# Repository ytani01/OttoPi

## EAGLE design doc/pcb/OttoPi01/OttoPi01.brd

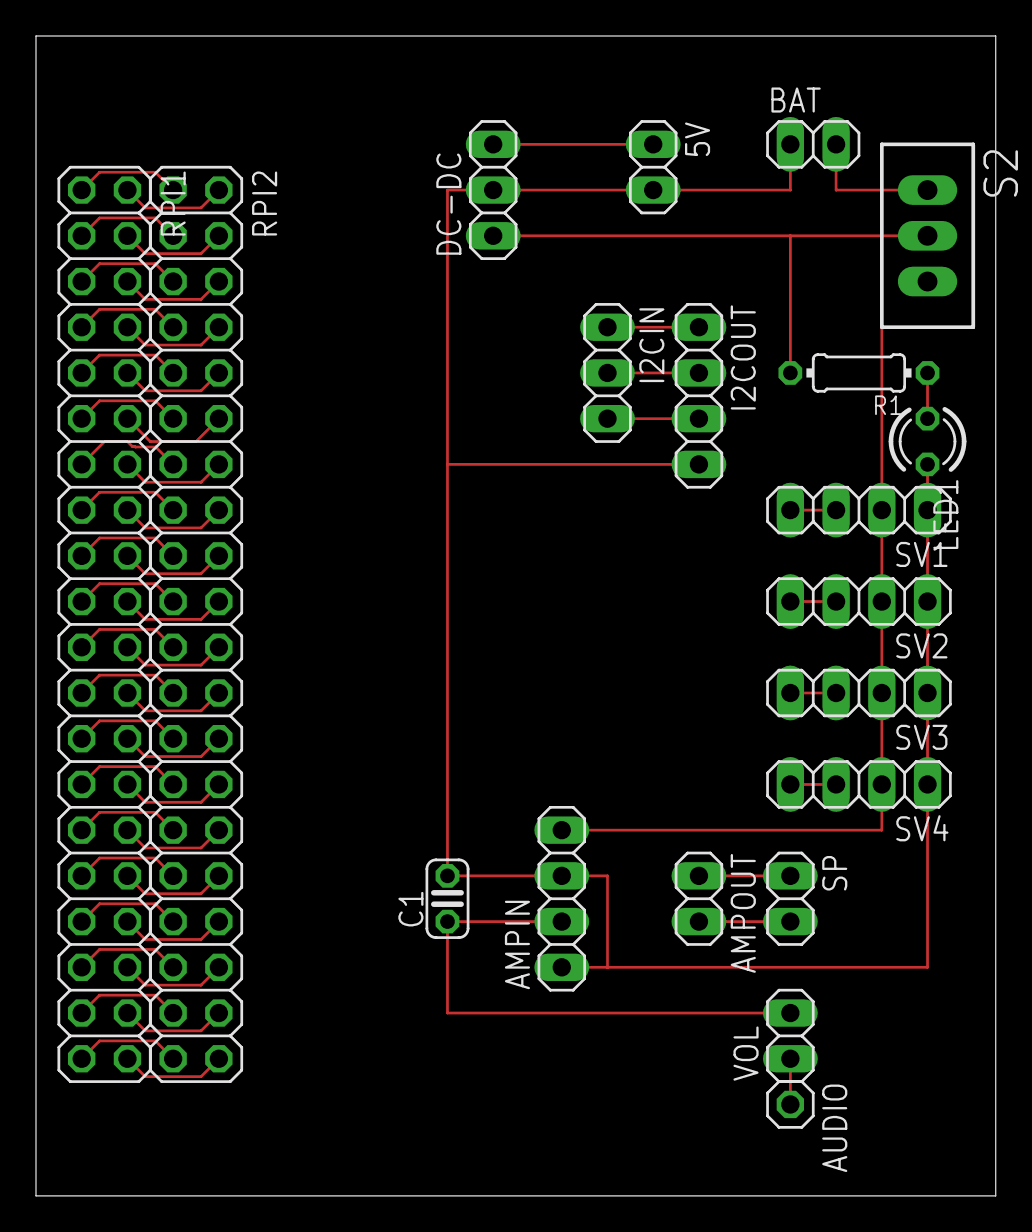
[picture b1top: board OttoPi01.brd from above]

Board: 2 copper layers, 53.3 x 64.4 mm, 20 parts (0 on the bottom side), 56 nets.

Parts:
5V: 1X02
AMPIN: 1X04
AMPOUT: 1X02
AUDIO: 1X01
BAT: 1X02
C1: C025-024X044
DC-DC: 1X03
I2CIN: 1X03
I2COUT: 1X04
LED1: LED3MM
R1: 0204/7
RPI1, RPI2: 2X20
S2: TL36PO; TL3XPO
SP: 1X02
SV1, SV2, SV3, SV4: 1X04
VOL: 1X02

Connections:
GND: 5V.2, AMPIN.1, AMPIN.3, BAT.1, C1.2, DC-DC.2, I2COUT.4, LED1.K, SV1.1, SV2.1, SV3.1, SV4.1
unnamed: I2CIN.1, I2COUT.1
unnamed: I2CIN.2, I2COUT.2
unnamed: I2CIN.3, I2COUT.3
unnamed: AMPOUT.2, SP.2
unnamed: 5V.1, DC-DC.3
unnamed: SV1.3, SV1.4
unnamed: BAT.2, S2.1
unnamed: AMPIN.2, C1.1, VOL.2
unnamed: SV2.3, SV2.4
unnamed: SV3.3, SV3.4
unnamed: SV4.3, SV4.4
unnamed: AMPOUT.1, SP.1
unnamed: AMPIN.4, DC-DC.1, R1.2, S2.2, SV1.2, SV2.2, SV3.2, SV4.2
unnamed: AUDIO.1, VOL.1
unnamed: LED1.A, R1.1
unnamed: RPI1.1, RPI2.1
unnamed: RPI1.3, RPI2.3
unnamed: RPI1.5, RPI2.5
unnamed: RPI1.7, RPI2.7
unnamed: RPI1.9, RPI2.9
unnamed: RPI1.11, RPI2.11
unnamed: RPI1.13, RPI2.13
unnamed: RPI1.15, RPI2.15
unnamed: RPI1.17, RPI2.17
unnamed: RPI1.19, RPI2.19
unnamed: RPI1.21, RPI2.21
unnamed: RPI1.23, RPI2.23
unnamed: RPI1.25, RPI2.25
unnamed: RPI1.27, RPI2.27
unnamed: RPI1.29, RPI2.29
unnamed: RPI1.31, RPI2.31
unnamed: RPI1.33, RPI2.33
unnamed: RPI1.35, RPI2.35
unnamed: RPI1.37, RPI2.37
unnamed: RPI1.39, RPI2.39
unnamed: RPI1.2, RPI2.2
unnamed: RPI1.4, RPI2.4
unnamed: RPI1.6, RPI2.6
unnamed: RPI1.8, RPI2.8
unnamed: RPI1.10, RPI2.10
unnamed: RPI1.12, RPI2.12
unnamed: RPI1.14, RPI2.14
unnamed: RPI1.16, RPI2.16
unnamed: RPI1.18, RPI2.18
unnamed: RPI1.20, RPI2.20
unnamed: RPI1.22, RPI2.22
unnamed: RPI1.24, RPI2.24
unnamed: RPI1.26, RPI2.26
unnamed: RPI1.28, RPI2.28
unnamed: RPI1.30, RPI2.30
unnamed: RPI1.32, RPI2.32
unnamed: RPI1.34, RPI2.34
unnamed: RPI1.36, RPI2.36
unnamed: RPI1.38, RPI2.38
unnamed: RPI1.40, RPI2.40

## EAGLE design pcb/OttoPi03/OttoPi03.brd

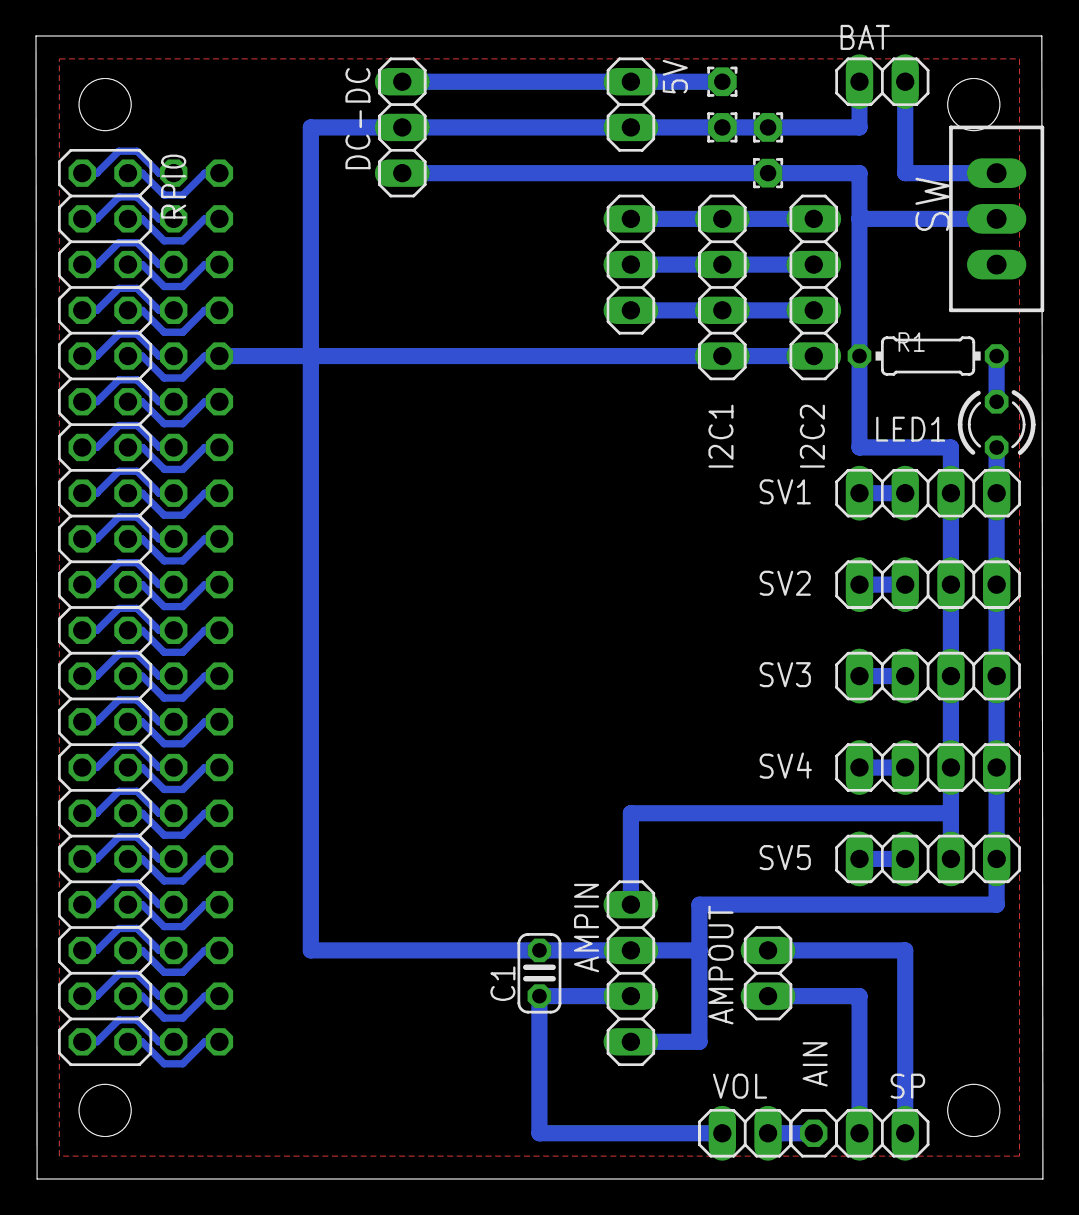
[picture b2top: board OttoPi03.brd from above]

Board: 2 copper layers, 55.9 x 63.5 mm, 26 parts (1 on the bottom side), 56 nets.

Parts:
5V: 1X02
5V_A: 1,6/0,9
AIN: 1X01
AMPIN: 1X04
AMPOUT: 1X02
BAT: 1X02
BAT_B: 1,6/0,9
C1: C025-024X044
DC-DC: 1X03
EXT: 2X20
GND_A: 1,6/0,9
GND_B: 1,6/0,9
I2C1, I2C2: 1X04
I2CIN: 1X03
LED1: LED3MM
R1: 0204/7
RPI0: 2X20
SP: 1X02
SV1, SV2, SV3, SV4, SV5: 1X04
SW: TL36PO; TL3XPO
VOL: 1X02

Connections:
3V3: I2C1.1, I2C2.1, I2CIN.1
4V: AMPIN.4, BAT_B.1, DC-DC.1, R1.2, SV1.2, SV2.2, SV3.2, SV4.2, SV5.2, SW.2
5V: 5V.1, 5V_A.1, DC-DC.3
AIN1: AIN.1, VOL.1
AIN2: AMPIN.2, C1.1, VOL.2
BAT+: BAT.2, SW.1
GND: 5V.2, AMPIN.1, AMPIN.3, BAT.1, C1.2, DC-DC.2, EXT.9, GND_A.1, GND_B.1, I2C1.4, I2C2.4, LED1.K, RPI0.10, SV1.1, SV2.1, SV3.1, SV4.1, SV5.1
unnamed: EXT.2, RPI0.1
unnamed: I2C1.2, I2C2.2, I2CIN.2
unnamed: I2C1.3, I2C2.3, I2CIN.3
unnamed: EXT.4, RPI0.3
unnamed: EXT.6, RPI0.5
unnamed: EXT.1, RPI0.2
unnamed: EXT.3, RPI0.4
unnamed: EXT.5, RPI0.6
unnamed: EXT.7, RPI0.8
unnamed: EXT.8, RPI0.7
unnamed: EXT.10, RPI0.9
unnamed: EXT.12, RPI0.11
unnamed: EXT.14, RPI0.13
unnamed: EXT.16, RPI0.15
unnamed: LED1.A, R1.1
unnamed: EXT.18, RPI0.17
unnamed: EXT.20, RPI0.19
unnamed: EXT.22, RPI0.21
unnamed: EXT.24, RPI0.23
unnamed: EXT.26, RPI0.25
unnamed: EXT.28, RPI0.27
unnamed: EXT.30, RPI0.29
unnamed: EXT.32, RPI0.31
unnamed: EXT.34, RPI0.33
unnamed: EXT.36, RPI0.35
unnamed: EXT.38, RPI0.37
unnamed: EXT.40, RPI0.39
unnamed: EXT.11, RPI0.12
unnamed: EXT.13, RPI0.14
unnamed: EXT.15, RPI0.16
unnamed: EXT.39, RPI0.40
unnamed: EXT.37, RPI0.38
unnamed: EXT.35, RPI0.36
unnamed: EXT.33, RPI0.34
unnamed: EXT.31, RPI0.32
unnamed: EXT.29, RPI0.30
unnamed: EXT.27, RPI0.28
unnamed: EXT.25, RPI0.26
unnamed: EXT.23, RPI0.24
unnamed: EXT.21, RPI0.22
unnamed: EXT.17, RPI0.18
unnamed: EXT.19, RPI0.20
SP+: AMPOUT.1, SP.1
SP-: AMPOUT.2, SP.2
SV1: SV1.3, SV1.4
SV2: SV2.3, SV2.4
SV3: SV3.3, SV3.4
SV4: SV4.3, SV4.4
SV5: SV5.3, SV5.4

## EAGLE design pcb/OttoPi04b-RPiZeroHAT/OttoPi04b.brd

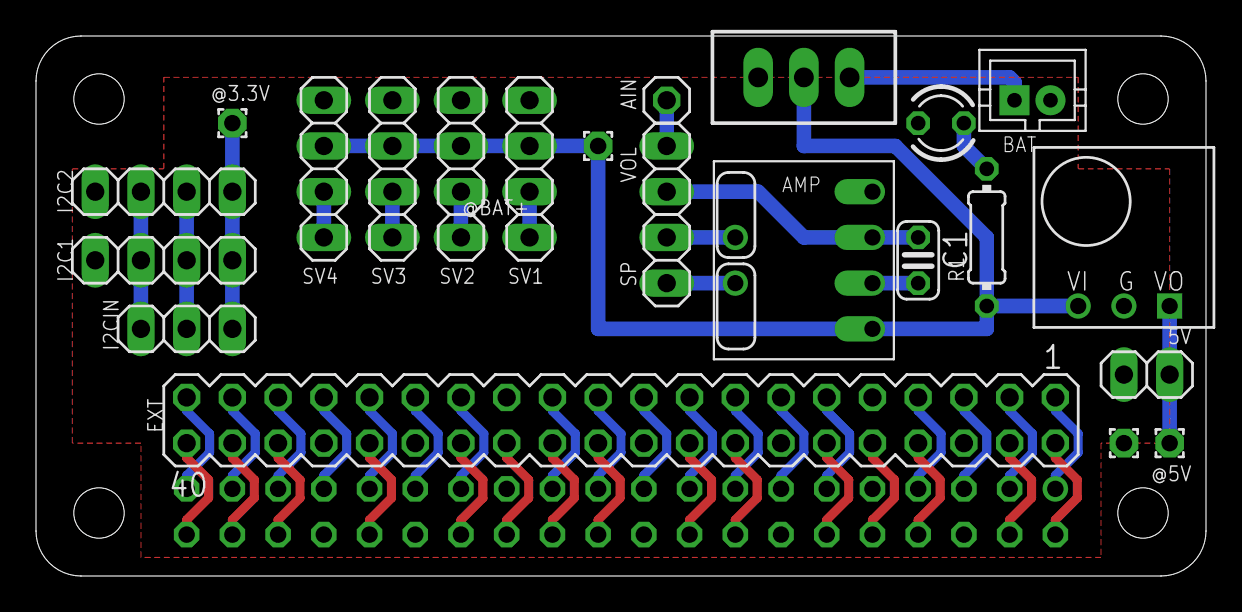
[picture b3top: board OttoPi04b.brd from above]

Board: 2 copper layers, 65.0 x 30.0 mm, 24 parts (1 on the bottom side), 48 nets.

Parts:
5V: 1X02
@3.3V, @5V: 1,6/0,9
@BAT+: 1,6/0,9
AIN: 1X01
AMP: PAM8012MOD; PAM8012MOD-A
BAT: JST-PH2
C1: C025-024X044
DCDC1: DCDC-5V-0.48A
EXT: MA20-2
I2C1, I2C2: 1X04
I2CIN: 1X03
LED1: LED3MM
PAD2: 1,6/0,9
R1: 1K; 0204/7
RPI: FE20-2
SP: 1X02
SV1, SV2, SV3, SV4: 1X04
SW: TL36PO; TL3XPO
VOL: 1X02

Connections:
+3V3: @3.3V.1, I2C1.1, I2C2.1, I2CIN.1
+3V3-S1: EXT.1, RPI.1
+3V3-S2: EXT.17, RPI.17
+4V_S: BAT.1, SW.1
+5V: 5V.2, @5V.1, DCDC1.+5V
+5V-S1: EXT.2, RPI.2
+5V-S2: EXT.4, RPI.4
AIN: AMP.IN+, C1.1, VOL.1
GND: 5V.1, AMP.GND, AMP.IN-, BAT.2, C1.2, DCDC1.GND, EXT.6, EXT.9, EXT.14, EXT.20, EXT.25, EXT.30, EXT.34, EXT.39, I2C1.4, I2C2.4, LED1.K, PAD2.1, RPI.6, RPI.9, RPI.14, RPI.20, RPI.25, RPI.30, RPI.34, RPI.39, SV1.1, SV2.1, SV3.1, SV4.1
GPIO0: EXT.27, RPI.27
GPIO1: EXT.28, RPI.28
GPIO4: EXT.7, RPI.7
GPIO5: EXT.29, RPI.29
GPIO6: EXT.31, RPI.31
GPIO7: EXT.26, RPI.26
GPIO8: EXT.24, RPI.24
GPIO9: EXT.21, RPI.21
GPIO10: EXT.19, RPI.19
GPIO11: EXT.23, RPI.23
GPIO12: EXT.32, RPI.32
GPIO13: EXT.33, RPI.33
GPIO14: EXT.8, RPI.8
GPIO15: EXT.10, RPI.10
GPIO16: EXT.36, RPI.36
GPIO17: EXT.11, RPI.11
GPIO18: EXT.12, RPI.12
GPIO19: EXT.35, RPI.35
GPIO20: EXT.38, RPI.38
GPIO21: EXT.40, RPI.40
GPIO22: EXT.15, RPI.15
GPIO23: EXT.16, RPI.16
GPIO24: EXT.18, RPI.18
GPIO25: EXT.22, RPI.22
GPIO26: EXT.37, RPI.37
GPIO27: EXT.13, RPI.13
LED: LED1.A, R1.1
unnamed: AIN.1, VOL.2
SCL: I2C1.3, I2C2.3, I2CIN.3
SCL-S: EXT.5, RPI.5
SDA-S: EXT.3, RPI.3
SDL: I2C1.2, I2C2.2, I2CIN.2
SP+: AMP.SP+@1, SP.1
SP-: AMP.SP-@1, SP.2
SV1: SV1.3, SV1.4
SV2: SV2.3, SV2.4
SV3: SV3.3, SV3.4
SV4: SV4.3, SV4.4
V+: @BAT+.1, AMP.V+, DCDC1.VIN, R1.2, SV1.2, SV2.2, SV3.2, SV4.2, SW.2
